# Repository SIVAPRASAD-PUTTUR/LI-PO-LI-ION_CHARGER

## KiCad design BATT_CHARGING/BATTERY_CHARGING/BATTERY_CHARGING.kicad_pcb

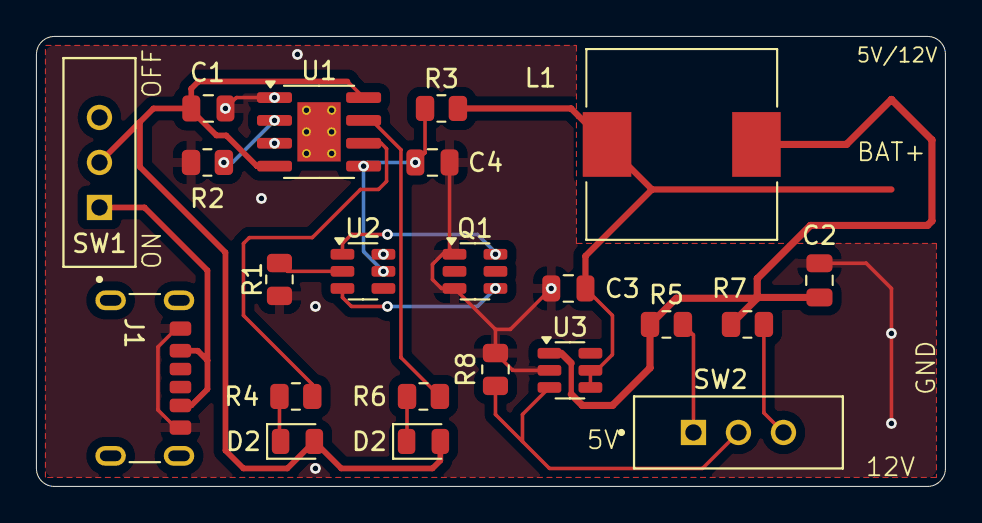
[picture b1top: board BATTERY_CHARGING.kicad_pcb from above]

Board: 2 copper layers, 50.5 x 25.0 mm, 22 parts (0 on the bottom side), 17 nets.

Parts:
C1: 10uF; C_0805_2012Metric
C2, C3: 22uF; C_0805_2012Metric
C4: 0.1uF; C_0805_2012Metric
D1: GREEN_LED; LED_0805_2012Metric
D2: RED_LED; LED_0805_2012Metric
J1: USB_C_6P; USB_C_Receptacle_GCT_USB4125-xx-x_6P_TopMnt_Horizontal
L1: L; L_10.4x10.4_H4.8
Q1: FS8205; SOT-23-6
R1, R8: 1K; R_0805_2012Metric
R2: 2K; R_0805_2012Metric
R3: 100E; R_0805_2012Metric
R4, R6: 220E; R_0805_2012Metric
R5: 7.3K; R_0805_2012Metric
R7: 20K; R_0805_2012Metric
SW1, SW2: SW_SPDT; SW_MINI-SPDT-SW
U1: TP4056; SOIC-8-1EP_3.9x4.9mm_P1.27mm_EP2.41x3.3mm_ThermalVias
U2: DW01A; SOT-23-6
U3: MT3608; SOT-23-6

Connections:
/BAT+: C3.1, L1.1, R3.2, U3.4 (EN), U3.5 (IN)
/OC: Q1.4, U2.3 (OC)
/OD: Q1.6, U2.1 (OD)
/VOUT: C2.1, L1.2, R5.1, R7.1, U3.1 (SW)
GND: C1.2, C2.2, C3.2, C4.2, J1.A12 (GND), J1.B12 (GND), Q1.1, Q1.3, R1.2, R2.2, R8.2, U1.1 (TEMP), U1.3 (GND), U2.6 (GND), U3.2 (GND)
unnamed: C1.1, D1.2 (A), D2.2 (A), SW1.2 (B), U1.4 (V_{CC}), U1.8 (CE)
unnamed: D2.1 (K), R6.2
unnamed: D1.1 (K), R4.1
unnamed: R5.2, SW2.1 (A)
unnamed: R8.1, SW2.2 (B), U3.3 (FB)
unnamed: R7.2, SW2.3 (C)
unnamed: J1.A9 (VBUS), J1.B9 (VBUS), SW1.1 (A)
unnamed: C4.1, R3.1, U1.5 (BAT), U2.5 (VCC)
unnamed: R2.1, U1.2 (PROG)
unnamed: R6.1, U1.7 (~CHRG)
unnamed: R4.2, U1.6 (~STDBY)
unnamed: R1.1, U2.2 (CS)
